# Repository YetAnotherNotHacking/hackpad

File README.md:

# HackPad
A simple pad of 8 switches for macros, using an RP2040 and Cherry MX switches.
Fun fact: designed everything in the lobby of GitHub HQ for HackClub Highway.
The firmware currently has the keys acting as if they were a numberpad 1-8.
The firmware should be modified for something more useful for whatever situation you want it to be used for.

## Overall HackPad
PCB is inside, but it's the same color

## Schematic

## PCB Schem

## Case assembly
I dont have a good screenshot, but you assemble the case by placing the PCB in the bottom and having it rest on the supports that are inside of it.

## Bill of Materials (BOM)

| Id | Designator                          | Footprint                         | Quantity | Designation       | Supplier and ref |
|----|-------------------------------------|-----------------------------------|----------|-------------------|------------------|
| 1  | U1                                  | XIAO-RP2350-DIP                   | 1        | XIAO-RP2040-DIP   |                  |
| 2  | SW8, SW7, SW6, SW5, SW4, SW3, SW2, SW1 | SW_Cherry_MX_1.00u_PCB           | 8        | SW_Push           |                  |
| 3  | D2, D1                               | LED_SK6812_PLCC4_5.0x5.0mm_P3.2mm | 2        | SK6812            |                  |

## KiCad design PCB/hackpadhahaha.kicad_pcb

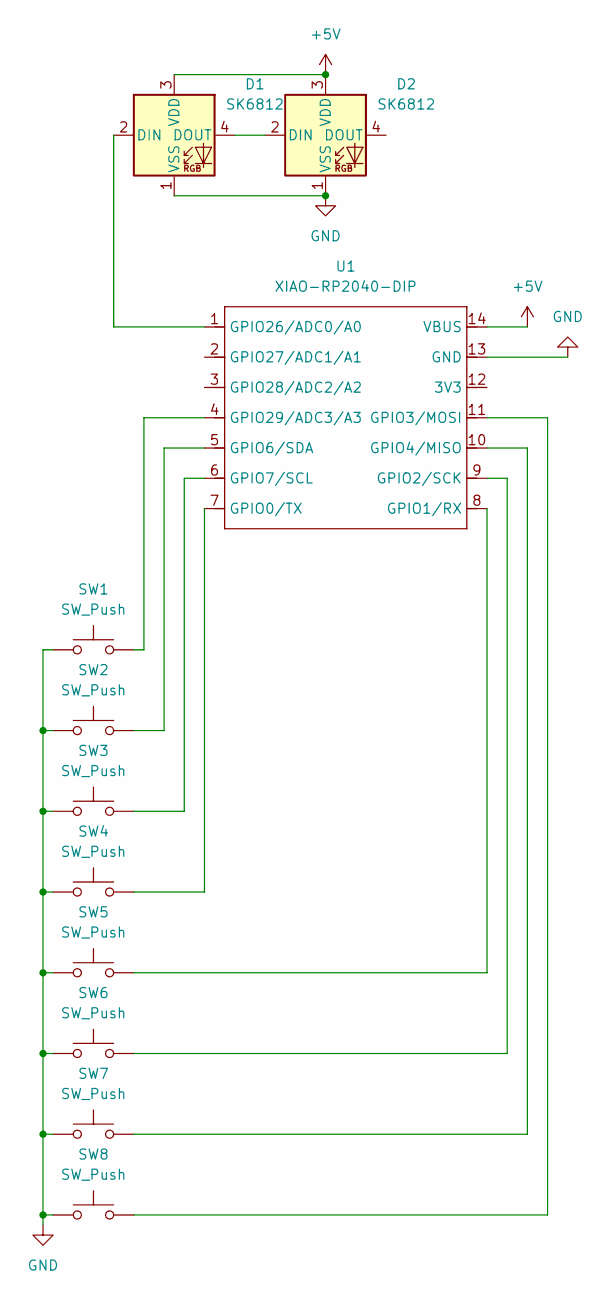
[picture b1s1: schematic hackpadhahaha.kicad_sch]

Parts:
D1, D2: SK6812; LED_SK6812_PLCC4_5.0x5.0mm_P3.2mm
SW1, SW2, SW3, SW4, SW5, SW6, SW7, SW8: SW_Push; SW_Cherry_MX_1.00u_PCB
U1: XIAO-RP2040-DIP; XIAO-RP2350-DIP

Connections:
+5V: D1.3 (VDD), D2.3 (VDD), U1.14 (VBUS)
GND: D1.1 (VSS), D2.1 (VSS), SW1.1, SW2.1, SW3.1, SW4.1, SW5.1, SW6.1, SW7.1, SW8.1, U1.13 (GND)
unnamed: D1.2 (DIN), U1.1 (GPIO26/ADC0/A0)
unnamed: D1.4 (DOUT), D2.2 (DIN)
unnamed: SW4.2, U1.7 (GPIO0/TX)
unnamed: SW5.2, U1.8 (GPIO1/RX)
unnamed: SW6.2, U1.9 (GPIO2/SCK)
unnamed: SW8.2, U1.11 (GPIO3/MOSI)
unnamed: SW7.2, U1.10 (GPIO4/MISO)
unnamed: SW2.2, U1.5 (GPIO6/SDA)
unnamed: SW3.2, U1.6 (GPIO7/SCL)
unnamed: SW1.2, U1.4 (GPIO29/ADC3/A3)

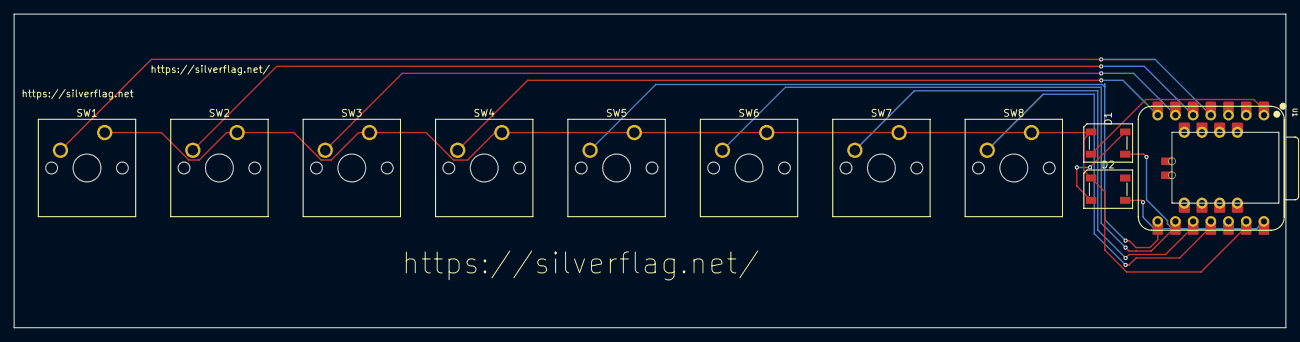
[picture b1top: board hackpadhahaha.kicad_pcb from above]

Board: 2 copper layers, 182.5 x 45.0 mm, 11 parts (0 on the bottom side), 12 nets.

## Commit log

2025-07-11 add case and other cad elemtns
2025-07-11 move to cad folder
2025-07-11 Upload PCB files
2025-07-11 fab exports
2025-07-12 fix naming
2025-07-12 add seperated files
    add seperated files
